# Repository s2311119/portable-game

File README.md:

# Portable RPG Console

Raspberry Pi Pico W（RP2040）で動作する、**自作の携帯型RPGゲーム機**です。

ゲームロジックだけでなく、LCD描画、物理ボタン入力、音声再生、SDカードへのセーブ／ロード、振動、3Dプリント用の筐体・ボタンまで含めて制作しました。

## 🎮 Demo

**[YouTubeでプレイ動画を見る](https://youtu.be/t7yi3DA9XdE)**

## Features

- 迷路・ダンジョンの自動生成
- ターン制バトル / ボス戦
- 仲間・スキル・装備・進化システム
- アイテム / ショップ / 宿屋 / 仲間の預かり
- SDカードへのセーブ / ロード
- BGM / SE / 振動
- 3Dプリント用の筐体・ボタン

## Hardware

- Raspberry Pi Pico W / RP2040
- ILI9341 320 × 240 LCD
- SD Card
- DACによる音声出力
- Physical Buttons
- Vibration Motor

## Technical Highlights

### メモリ制約を考慮したLCD描画

320 × 240画面全体のフレームバッファを持つのではなく、**320 × 32 pxのline sprite**を使って画面を分割描画しています。

限られたRAM上で、フィールド・戦闘・各種メニューを描画できる構成にしています。

### RP2040のマルチコアを利用した音声処理

ゲーム処理とは別にRP2040のもう一方のcoreを音声処理に利用しています。

SDカードから読み込んだBGMの再生と、リアルタイムに生成するSEを組み合わせて出力しています。

### Procedural Map Generation

探索マップは固定マップだけでなく、アルゴリズムによる自動生成に対応しています。

迷路生成をベースに、部屋・階段・宝箱・敵とのエンカウントなどを組み合わせてダンジョンを構成しています。

### Software Architecture

開発初期は多くの処理が単一の `.ino` に集中していましたが、規模の拡大に合わせて責務を分離しました。

```text
Game
├─ GameSession
├─ Exploration / Battle / MenuFlow
├─ Game Systems
├─ Renderers
└─ Audio / Storage / Input / Graphics
```

ゲームロジックからLCD・SD・Audioなどのハードウェア依存処理を分離し、Rendererもゲーム状態を変更しないread-onlyな構造にしています。

最終的にはArduino側のentry pointをシンプルにし、ゲーム全体の制御を `Game` 以下へ集約しました。

```cpp
void setup() {
    Game::boot();
}

void loop() {
    ctx->update();
}
```

## Tech Stack

`C++` `Arduino` `RP2040` `LovyanGFX` `SdFat` `Fusion 360`

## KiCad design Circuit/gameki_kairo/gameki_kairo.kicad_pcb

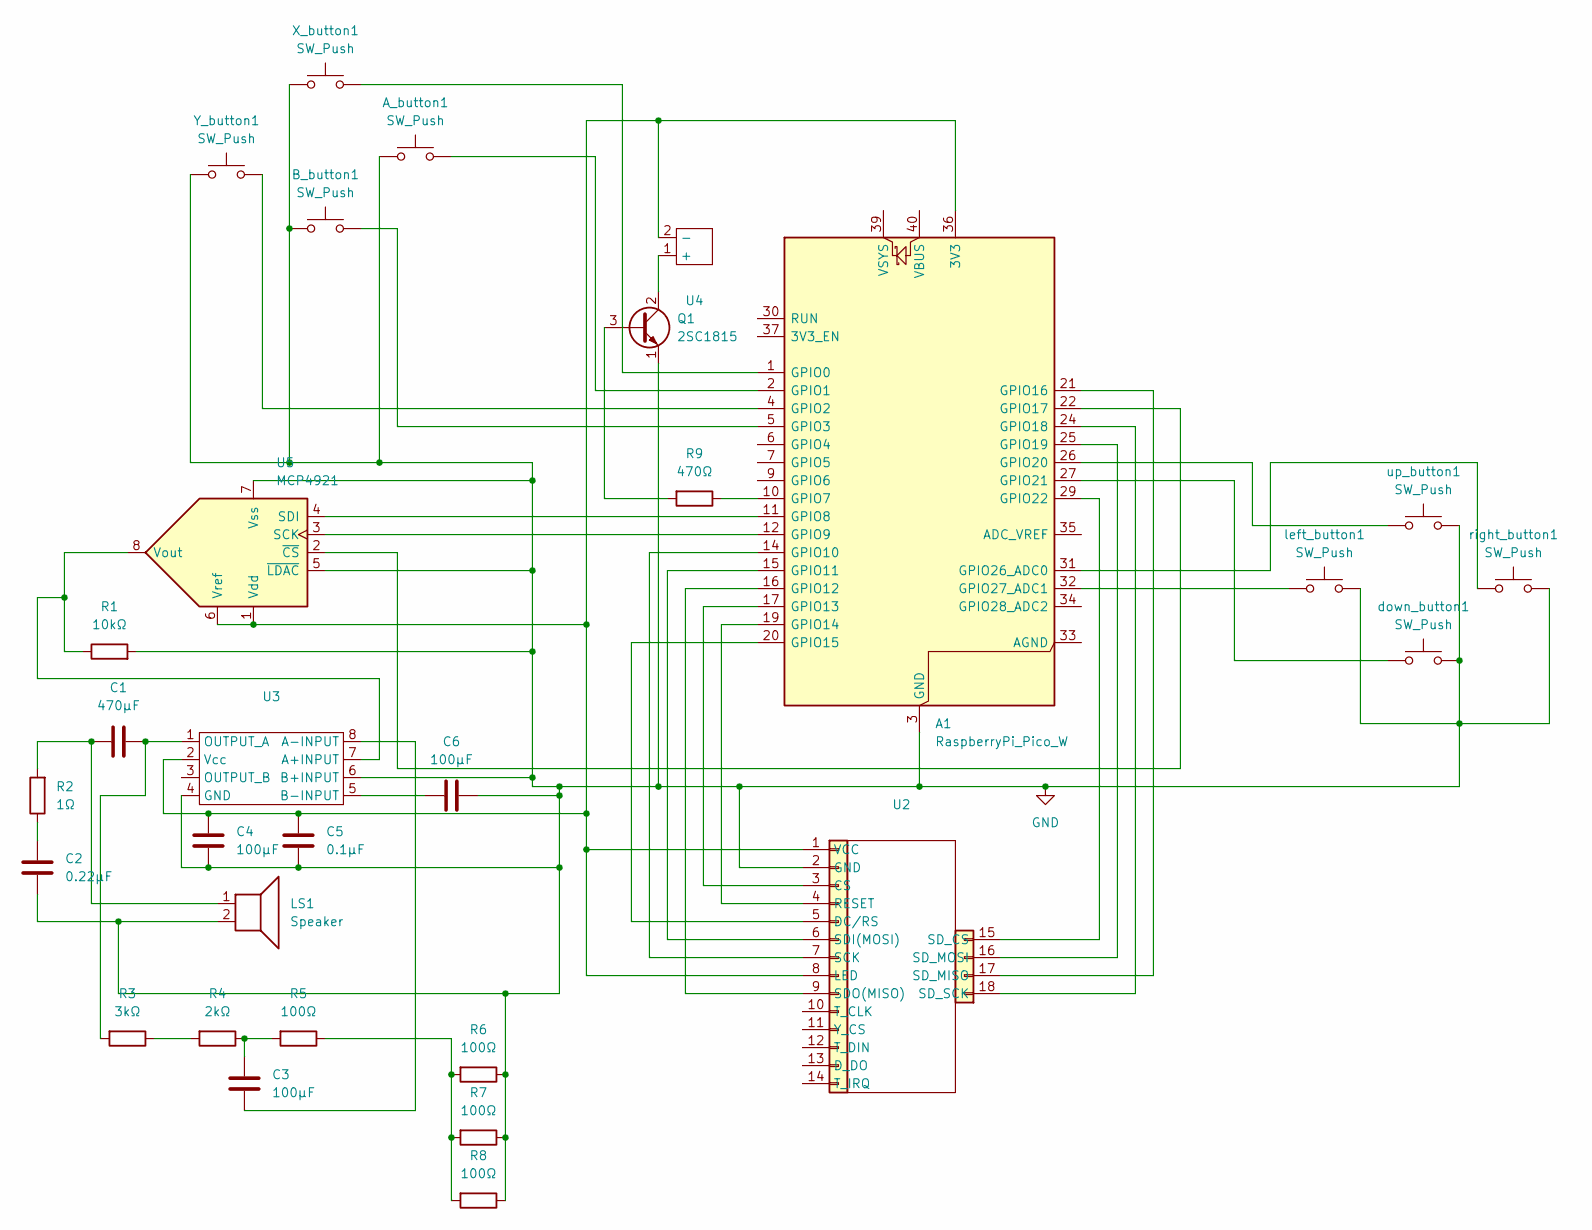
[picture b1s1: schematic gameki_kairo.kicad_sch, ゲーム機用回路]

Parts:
A1: RaspberryPi_Pico_W; RaspberryPi_Pico_Common_THT
A_button1: SW_Push; SW_MEC_5GTH9
B_button1: SW_Push; SW_MEC_5GTH9
C1: 470µF; CP_Radial_D10.0mm_P7.50mm
C2: 0.22µF; C_Disc_D5.0mm_W2.5mm_P5.00mm
C3: 100µF; CP_Radial_D4.0mm_P2.00mm
C4: 100µF; CP_Radial_Tantal_D6.0mm_P5.00mm
C5: 0.1µF; C_Disc_D8.0mm_W5.0mm_P5.00mm
C6: 100µF; CP_Radial_D6.3mm_P2.50mm
LS1: Speaker; Speaker_1
Q1: 2SC1815; TO-92_Inline
R1: 10kΩ; R_Axial_DIN0207_L6.3mm_D2.5mm_P7.62mm_Horizontal
R2: 1Ω; R_Axial_DIN0207_L6.3mm_D2.5mm_P7.62mm_Horizontal
R3: 3kΩ; R_Axial_DIN0207_L6.3mm_D2.5mm_P7.62mm_Horizontal
R4: 2kΩ; R_Axial_DIN0207_L6.3mm_D2.5mm_P7.62mm_Horizontal
R5, R6, R7, R8: 100Ω; R_Axial_DIN0207_L6.3mm_D2.5mm_P7.62mm_Horizontal
R9: 470Ω; R_Axial_DIN0207_L6.3mm_D2.5mm_P7.62mm_Horizontal
U2: MSP2807_1
U3: M2073_1_foot
U4: ブラシレス振動モーター
U5: MCP4921; DIP-8_W7.62mm
X_button1: SW_Push; SW_MEC_5GTH9
Y_button1: SW_Push; SW_MEC_5GTH9
down_button1: SW_Push; SW_MEC_5GTH9
left_button1: SW_Push; SW_MEC_5GTH9
right_button1: SW_Push; SW_MEC_5GTH9
up_button1: SW_Push; SW_MEC_5GTH9

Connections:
GND: A1.3 (GND), A1.8 (GND), A1.13 (GND), A1.18 (GND), A1.23 (GND), A1.28 (GND), A1.38 (GND), A_button1.1, B_button1.1, C2.1, C4.2, C5.1, C6.2, LS1.2, Q1.1 (E), R1.2, R6.1, R7.1, R8.1, U2.2 (GND), U3.4 (GND), U3.6 (B+INPUT), U5.5 (~LDAC), U5.7 (Vss), X_button1.1, Y_button1.1, down_button1.2, left_button1.2, right_button1.2, up_button1.2
unnamed: A1.36 (3V3), C4.1, C5.2, U2.1 (VCC), U2.8 (LED), U3.2 (Vcc), U4.2 (-), U5.1 (Vdd), U5.6 (Vref)
unnamed: A1.1 (GPIO0), X_button1.2
unnamed: A1.2 (GPIO1), A_button1.2
unnamed: A1.4 (GPIO2), Y_button1.2
unnamed: A1.5 (GPIO3), B_button1.2
unnamed: A1.10 (GPIO7), R9.1
unnamed: A1.11 (GPIO8), U5.4 (SDI)
unnamed: A1.12 (GPIO9), U5.3 (SCK)
unnamed: A1.14 (GPIO10), U2.7 (SCK)
unnamed: A1.15 (GPIO11), U2.6 (SDI(MOSI))
unnamed: A1.16 (GPIO12), U2.9 (SDO(MISO))
unnamed: A1.17 (GPIO13), U2.3 (CS)
unnamed: A1.19 (GPIO14), U2.4 (RESET)
unnamed: A1.20 (GPIO15), U2.5 (DC/RS)
unnamed: A1.21 (GPIO16), U2.17 (SD_MISO)
unnamed: A1.22 (GPIO17), U5.2 (~CS)
unnamed: A1.24 (GPIO18), U2.18 (SD_SCK)
unnamed: A1.25 (GPIO19), U2.16 (SD_MOSI)
unnamed: A1.26 (GPIO20), up_button1.1
unnamed: A1.27 (GPIO21), down_button1.1
unnamed: A1.29 (GPIO22), U2.15 (SD_CS)
unnamed: A1.31 (GPIO26_ADC0), right_button1.1
unnamed: A1.32 (GPIO27_ADC1), left_button1.1
unnamed: C1.1, LS1.1, R2.2
unnamed: C2.2, R2.1
unnamed: C3.2, R4.1, R5.2
unnamed: Q1.3 (B), R9.2
unnamed: Q1.2 (C), U4.1 (+)
unnamed: R3.1, R4.2
unnamed: R5.1, R6.2, R7.2, R8.2
unnamed: R1.1, U3.7 (A+INPUT), U5.8 (Vout)
unnamed: C3.1, U3.8 (A-INPUT)
unnamed: C6.1, U3.5 (B-INPUT)
unnamed: C1.2, R3.2, U3.1 (OUTPUT_A)

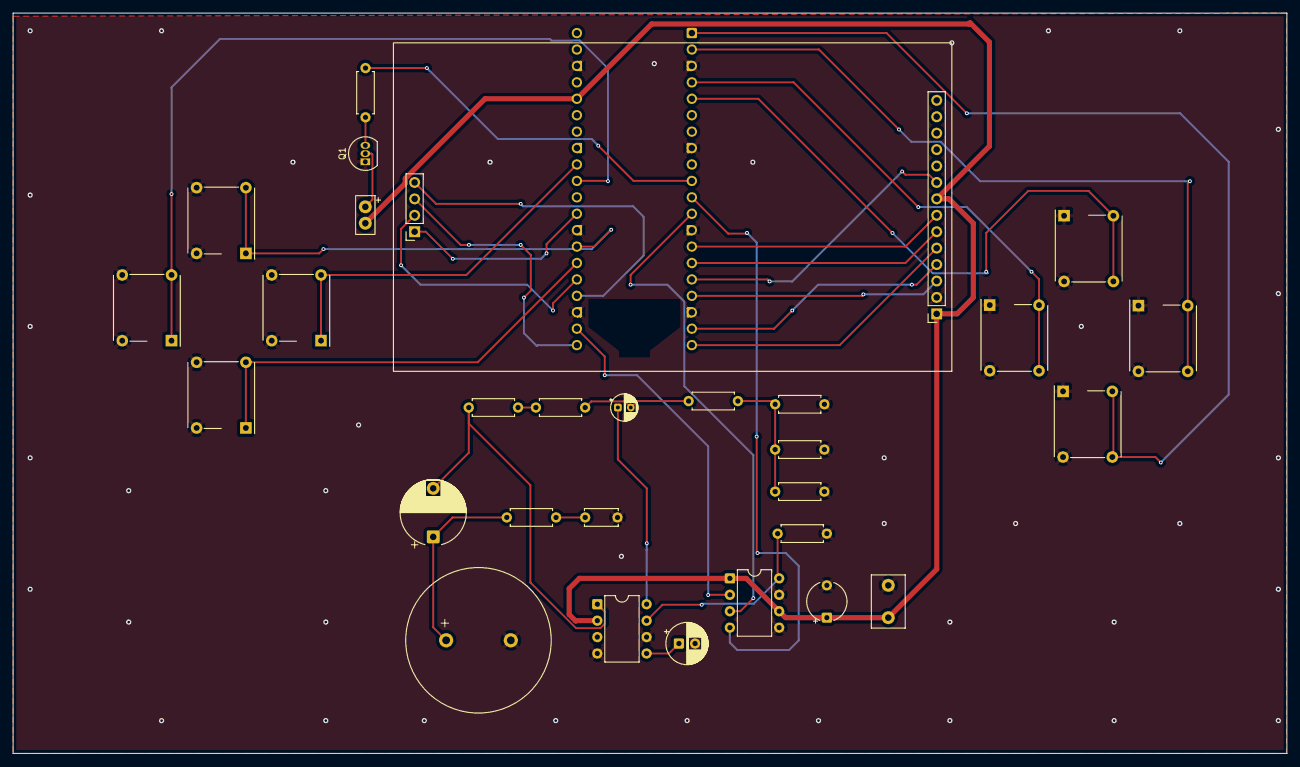
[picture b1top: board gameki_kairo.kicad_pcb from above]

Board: 2 copper layers, 197.0 x 114.5 mm, 30 parts (1 on the bottom side), 35 nets.
